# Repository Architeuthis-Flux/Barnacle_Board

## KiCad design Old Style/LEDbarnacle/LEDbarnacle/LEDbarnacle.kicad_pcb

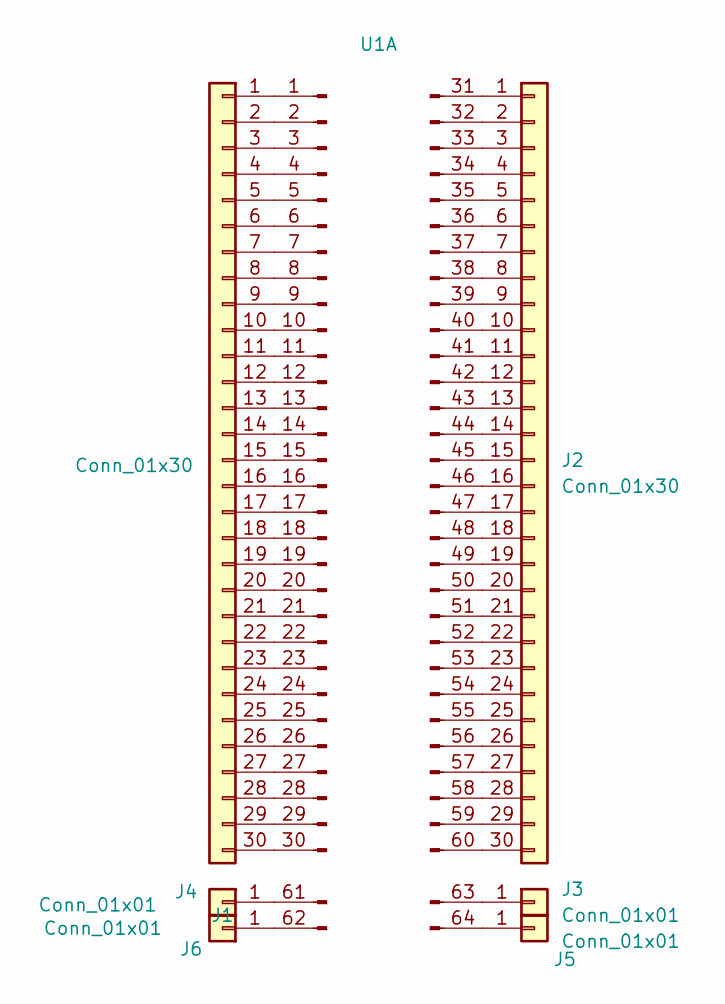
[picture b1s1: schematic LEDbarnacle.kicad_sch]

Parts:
J1, J2: Conn_01x30; ProtoboardRow
J3, J4, J5, J6: Conn_01x01; ProtoPower
U1: HEE70LP03BK_CardSide

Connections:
unnamed: J1.1, U1.1
unnamed: J1.2, U1.2
unnamed: J1.3, U1.3
unnamed: J1.4, U1.4
unnamed: J1.5, U1.5
unnamed: J1.6, U1.6
unnamed: J1.7, U1.7
unnamed: J1.8, U1.8
unnamed: J1.9, U1.9
unnamed: J1.10, U1.10
unnamed: J1.11, U1.11
unnamed: J1.12, U1.12
unnamed: J1.13, U1.13
unnamed: J1.14, U1.14
unnamed: J1.15, U1.15
unnamed: J1.16, U1.16
unnamed: J1.17, U1.17
unnamed: J1.18, U1.18
unnamed: J1.19, U1.19
unnamed: J1.20, U1.20
unnamed: J1.21, U1.21
unnamed: J1.22, U1.22
unnamed: J1.23, U1.23
unnamed: J1.24, U1.24
unnamed: J1.25, U1.25
unnamed: J1.26, U1.26
unnamed: J1.27, U1.27
unnamed: J1.28, U1.28
unnamed: J1.29, U1.29
unnamed: J1.30, U1.30
unnamed: J2.1, U1.31
unnamed: J2.2, U1.32 (Pin_0)
unnamed: J2.3, U1.33 (Pin_1)
unnamed: J2.4, U1.34 (Pin_2)
unnamed: J2.5, U1.35 (Pin_3)
unnamed: J2.6, U1.36 (Pin_4)
unnamed: J2.7, U1.37 (Pin_5)
unnamed: J2.8, U1.38 (Pin_6)
unnamed: J2.9, U1.39 (Pin_7)
unnamed: J2.10, U1.40 (Pin_8)
unnamed: J2.11, U1.41 (Pin_9)
unnamed: J2.12, U1.42 (Pin_10)
unnamed: J2.13, U1.43 (Pin_11)
unnamed: J2.14, U1.44 (Pin_12)
unnamed: J2.15, U1.45 (Pin_13)
unnamed: J2.16, U1.46 (Pin_14)
unnamed: J2.17, U1.47 (Pin_15)
unnamed: J2.18, U1.48 (Pin_16)
unnamed: J2.19, U1.49 (Pin_17)
unnamed: J2.20, U1.50 (Pin_18)
unnamed: J2.21, U1.51 (Pin_19)
unnamed: J2.22, U1.52 (Pin_20)
unnamed: J2.23, U1.53 (Pin_21)
unnamed: J2.24, U1.54 (Pin_22)
unnamed: J2.25, U1.55 (Pin_23)
unnamed: J2.26, U1.56 (Pin_24)
unnamed: J2.27, U1.57 (Pin_25)
unnamed: J2.28, U1.58 (Pin_26)
unnamed: J2.29, U1.59 (Pin_27)
unnamed: J2.30, U1.60 (Pin_28)
unnamed: J3.1, U1.63 (Bot_Pos)
unnamed: J4.1, U1.61 (Top_Pos)
unnamed: J5.1, U1.64 (Bot_Neg)
unnamed: J6.1, U1.62 (Top_Neg)

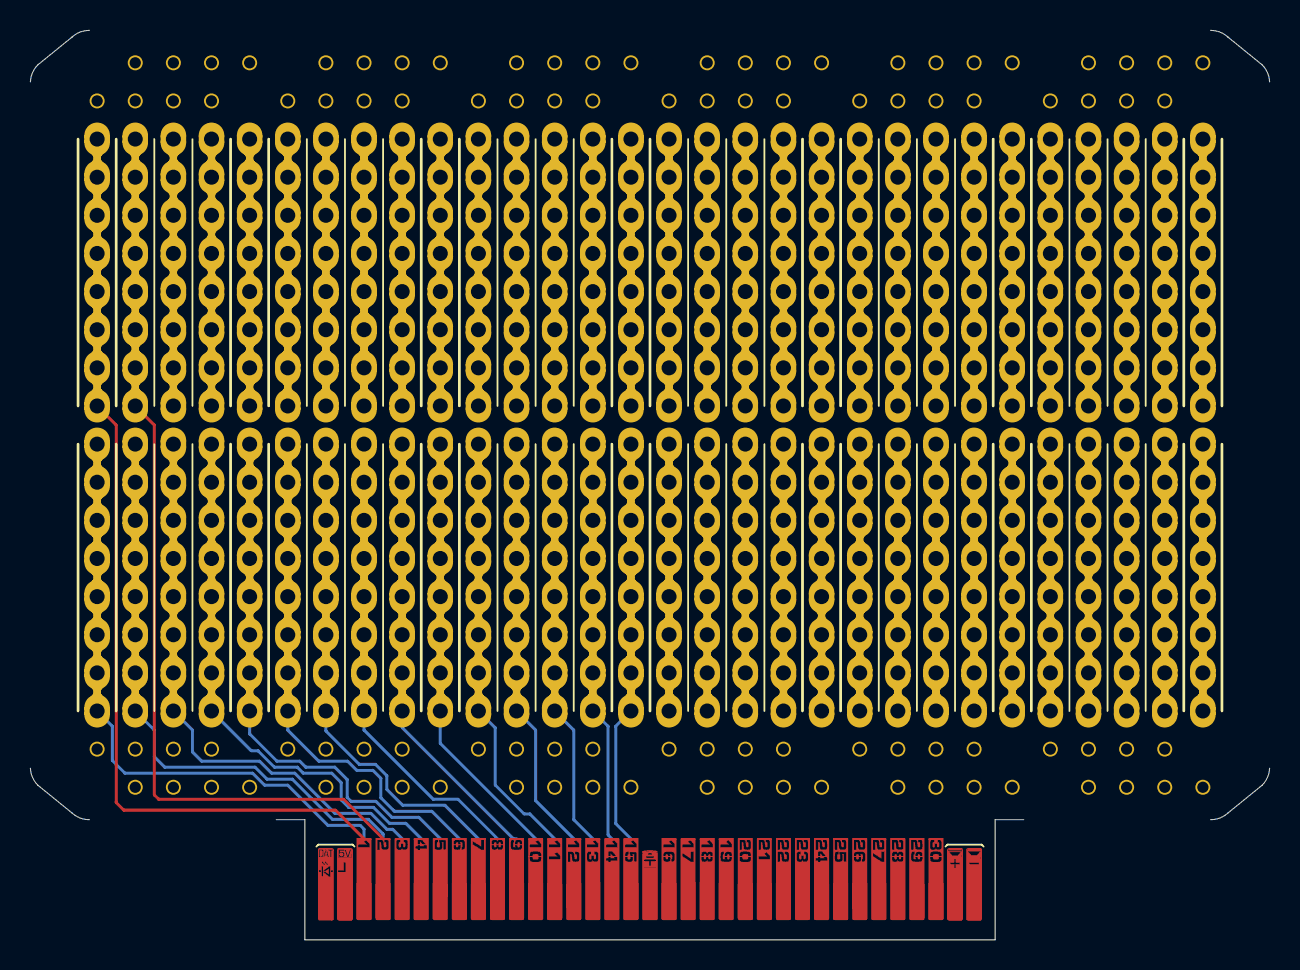
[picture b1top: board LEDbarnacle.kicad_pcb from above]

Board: 4 copper layers, 82.6 x 60.6 mm, 7 parts (0 on the bottom side), 64 nets.

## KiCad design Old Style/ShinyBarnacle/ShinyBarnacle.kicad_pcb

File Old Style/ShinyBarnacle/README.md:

# Shiny Barnacle

The Shiny Barnacle doesn't interact with the breadboard directly, but provides driver for the LEDs and a way to load/store different circuits from text files loaded into the RP2040's flash over USB, with some buttons and a knob for selecting and making nets. They can also include sequence information so a teacher can load a lab onto the students' boards and each step for building a circuit will be lit up as they build it.

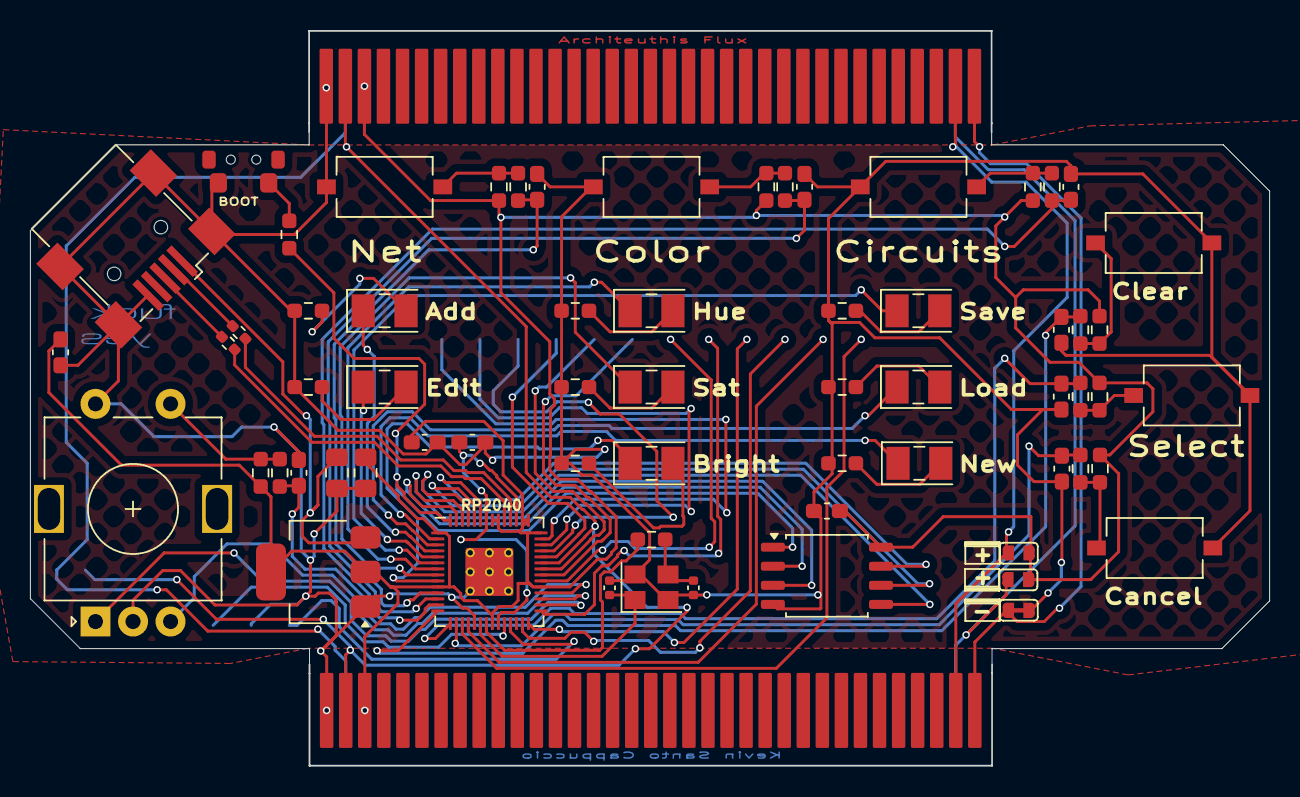
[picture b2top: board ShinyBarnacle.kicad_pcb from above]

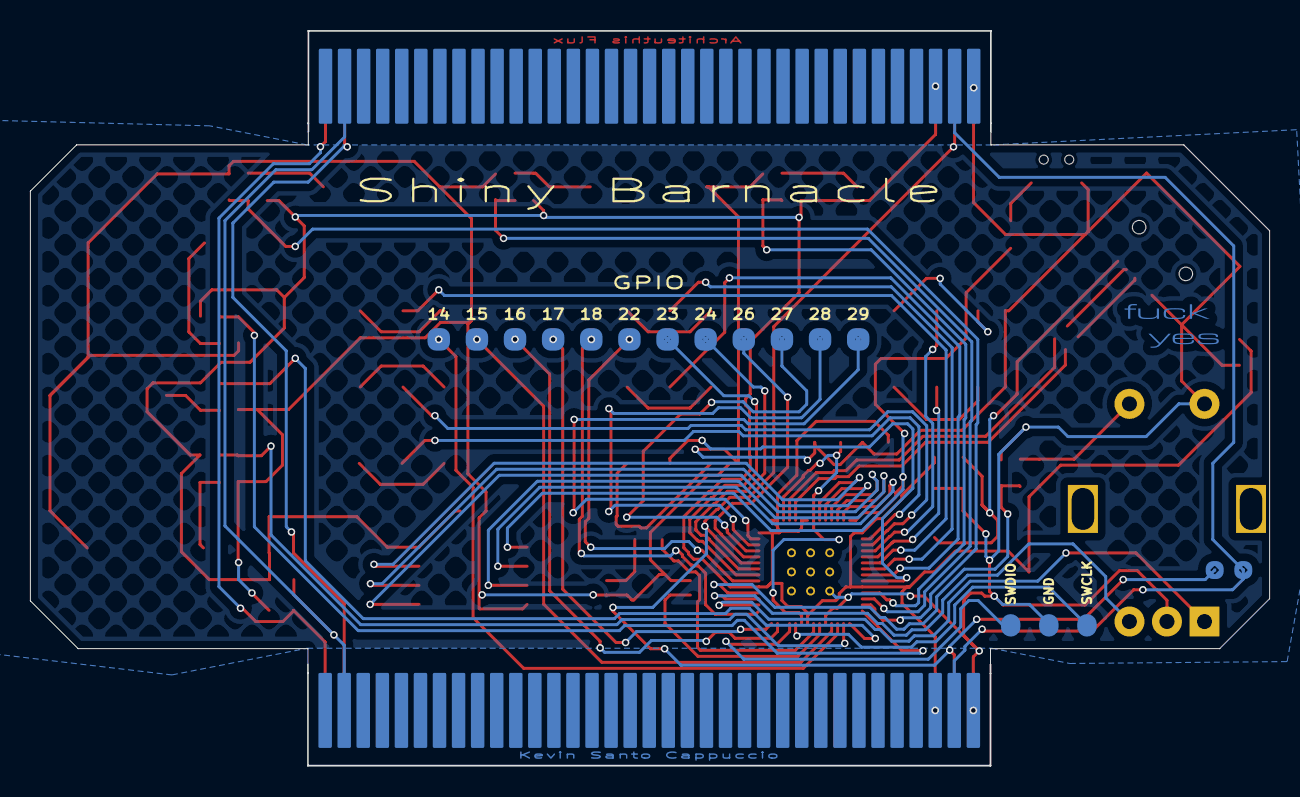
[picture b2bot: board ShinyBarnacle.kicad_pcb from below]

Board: 2 copper layers, 82.5 x 48.9 mm, 82 parts (15 on the bottom side), 130 nets.

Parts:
C1, C2: 27p; C_0402_1005Metric
C3, C5, C7, C9: 1u; C_0603_1608Metric_Pad1.08x0.95mm_HandSolder
C4, C6: 10u; C_0805_2012Metric_Pad1.18x1.45mm_HandSolder
C10, C11, C12, C13, C14, C15, C16: 0.1uF; C_0603_1608Metric_Pad1.08x0.95mm_HandSolder
D2, D3, D4, D5, D6, D7, D8, D9: LED; LED_PLCC-2_3x2mm_AK
J1: USB_B_Mini; USB_Mini-B_Wuerth_65100516121_Horizontal
J2: Debug; PinHeader_1x03_P2.54mm_Vertical
J3: Conn_02x35_JumperluxCardEdge; HEE70LP03BK_Daughter_Penis_Top
J4: Conn_02x35_JumperluxCardEdge; HEE70LP03BK_Daughter_Penis
JP1: SolderJumper_2_Bridged; SolderJumper_2_Bridged_Small
JP2, JP3: Power_From_Breadboard; SolderJumper_2_Open_Small
R1, R2: 1k; R_0603_1608Metric_Pad0.98x0.95mm_HandSolder
R3, R4: 22R; R_0402_1005Metric_Pad0.72x0.64mm_HandSolder
R5, R6, R7, R8, R9, R10, R11, R12: 1K; R_0603_1608Metric_Pad0.98x0.95mm_HandSolder
R13, R21, R22, R23, R24, R25, R26: 47K; R_0603_1608Metric_Pad0.98x0.95mm_HandSolder
R14, R15, R16, R17, R18, R19, R20: 10K; R_0603_1608Metric_Pad0.98x0.95mm_HandSolder
SW1: USB BOOT; Tact_Switch_TS24CA
SW3: Select Row; RotaryEncoder_Alps_EC11E-Switch_Vertical_H20mm
SW4, SW5, SW6, SW7, SW8, SW9: SW_Push; SW_Tactile_SPST_NO_Straight_CK_PTS636Sx25SMTRLFS
TP1, TP2, TP3, TP4, TP5, TP6, TP7, TP8, TP9, TP10, TP11, TP12: TestPoint; TestPoint_Pad_D1.0mm
TP13, TP14: TestPoint; TestPoint_D0.75mm
U1: W25Q128JVS; SOIC-8_5.23x5.23mm_P1.27mm
U2: NCP1117-3.3_SOT223; SOT-223-3_TabPin2
U3: RP2040; RP2040-QFN-56
Y1: ABLS-12.000MHZ-B4-T; Crystal_SMD_3225-4Pin_3.2x2.5mm

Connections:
1: J3.31, J4.31
2: J3.32, J4.32
3: J3.33, J4.33
4: J3.34, J4.34
5: J3.35, J4.35
6: J3.36, J4.36
7: J3.37, J4.37
8: J3.38, J4.38
9: J3.39, J4.39
10: J3.40, J4.40
11: J3.41, J4.41
12: J3.42, J4.42
13: J3.43, J4.43
14: J3.44, J4.44
15: J3.45, J4.45
16: J3.46, J4.46
17: J3.47, J4.47
18: J3.48, J4.48
19: J3.49, J4.49
20: J3.50, J4.50
21: J3.51, J4.51
22: J3.52, J4.52
23: J3.53, J4.53
24: J3.54, J4.54
25: J3.55, J4.55
26: J3.56, J4.56
27: J3.57, J4.57
28: J3.58, J4.58
29: J3.59, J4.59
30: J3.60, J4.60
31: J3.1, J4.1
32: J3.2, J4.2
33: J3.3, J4.3
34: J3.4, J4.4
35: J3.5, J4.5
36: J3.6, J4.6
37: J3.7, J4.7
38: J3.8, J4.8
39: J3.9, J4.9
40: J3.10, J4.10
41: J3.11, J4.11
42: J3.12, J4.12
43: J3.13, J4.13
44: J3.14, J4.14
45: J3.15, J4.15
46: J3.16, J4.16
47: J3.17, J4.17
48: J3.18, J4.18
49: J3.19, J4.19
50: J3.20, J4.20
51: J3.21, J4.21
52: J3.22, J4.22
53: J3.23, J4.23
54: J3.24, J4.24
55: J3.25, J4.25
56: J3.26, J4.26
57: J3.27, J4.27
58: J3.28, J4.28
59: J3.29, J4.29
60: J3.30, J4.30
+1V1: C7.1, U3.23 (DVDD), U3.45 (VREG_VOUT), U3.50 (DVDD)
+5V: C4.1, J1.1 (VBUS), U2.3 (VI)
/QSPI_SCLK: U1.6 (CLK), U3.52 (QSPI_SCLK)
/QSPI_SD0: U1.5 (DI(IO0)), U3.53 (QSPI_SD0)
/QSPI_SD1: U1.2 (DO(IO1)), U3.55 (QSPI_SD1)
/QSPI_SD2: U1.3 (IO2), U3.54 (QSPI_SD2)
/QSPI_SD3: U1.7 (IO3), U3.51 (QSPI_SD3)
/QSPI_SS: R1.1, U1.1 (~CS), U3.56 (QSPI_SS)
/SWCLK: J2.1, U3.24 (SWCLK)
/SWD: J2.3, U3.25 (SWD)
/USB_D+: J1.3 (D+), R3.1
/USB_D-: J1.2 (D-), R4.1
/XIN: C1.1, U3.20 (XIN), Y1.1
/XOUT: R2.1, U3.21 (XOUT)
/~USB_BOOT: R1.2, SW1.2
BOTTOM_RAIL_NEG: J3.62, J4.62
BOTTOM_RAIL_POS: J3.61, J4.61, JP3.1 (A)
Button_Cancel: C14.1, R18.1, U3.16 (GPIO13)
Button_Circuits: C12.1, R16.1, U3.13 (GPIO10)
Button_Clear: C11.1, R15.1, U3.14 (GPIO11)
Button_Color: C15.1, R19.1, U3.12 (GPIO9)
Button_Net: C16.1, R20.1, U3.11 (GPIO8)
Button_Select: C13.1, R17.1, U3.15 (GPIO12)
ENC_1_A: SW3.A, U3.30 (GPIO19)
ENC_1_B: SW3.B, U3.31 (GPIO20)
ENC_1_Button: C10.1, R14.1, U3.32 (GPIO21)
GPIO_14: TP1.1, U3.17 (GPIO14)
GPIO_15: TP2.1, U3.18 (GPIO15)
GPIO_18: TP5.1, U3.29 (GPIO18)
GPIO_22: TP8.1, U3.34 (GPIO22)
GPIO_23: TP9.1, U3.35 (GPIO23)
GPIO_24: TP10.1, U3.36 (GPIO24)
GPIO_26: TP11.1, U3.38 (GPIO26_ADC0)
GPIO_27: TP12.1, U3.39 (GPIO27_ADC1)
GPIO_28: TP6.1, U3.40 (GPIO28_ADC2)
GPIO_29: TP7.1, U3.41 (GPIO29_ADC3)
LED_0: D2.2 (A), U3.2 (GPIO0)
LED_1: D3.2 (A), U3.3 (GPIO1)
LED_2: D4.2 (A), U3.4 (GPIO2)
LED_3: D5.2 (A), U3.5 (GPIO3)
LED_4: D6.2 (A), U3.6 (GPIO4)
LED_5: D7.2 (A), U3.7 (GPIO5)
LED_5V: C3.1, C5.1, C6.1, C9.1, J3.67, J3.70, J4.67, J4.70, JP2.2 (B), JP3.2 (B), R13.2, R21.2, R22.2, R23.2, R24.2, R25.2, R26.2, U1.8 (VCC), U2.2 (VO), U3.1 (IOVDD), U3.10 (IOVDD), U3.22 (IOVDD), U3.33 (IOVDD), U3.42 (IOVDD), U3.43 (ADC_AVDD), U3.44 (VREG_IN), U3.48 (USB_VDD), U3.49 (IOVDD)
LED_6: D8.2 (A), U3.8 (GPIO6)
LED_7: D9.2 (A), U3.9 (GPIO7)
LED_DATA_IN: J3.69, J4.69, TP13.1
LED_DATA_OUT: J3.66, J4.66, TP14.1, U3.37 (GPIO25)
LED_GND: C1.2, C2.2, C3.2, C4.2, C5.2, C6.2, C7.2, C9.2, C10.2, C11.2, C12.2, C13.2, C14.2, C15.2, C16.2, J1.5 (GND), J1.6 (Shield), J2.2, J3.65, J3.68, J4.65, J4.68, JP1.1 (A), R5.2, R6.2, R7.2, R8.2, R9.2, R10.2, R11.2, R12.2, SW1.1, SW3.C, SW3.S2, SW4.1, SW5.1, SW6.1, SW7.1, SW8.1, SW9.1, U1.4 (GND), U2.1 (GND), U3.19 (TESTEN), U3.57 (GND), Y1.2, Y1.4
unnamed: C2.1, R2.2, Y1.3
unnamed: D2.1 (K), R5.1
unnamed: D3.1 (K), R6.1
unnamed: D4.1 (K), R7.1
unnamed: D5.1 (K), R8.1
unnamed: D6.1 (K), R9.1
unnamed: D7.1 (K), R10.1
unnamed: D8.1 (K), R11.1
unnamed: D9.1 (K), R12.1
unnamed: R13.1, R14.2, SW3.S1
unnamed: R15.2, R21.1, SW4.2
unnamed: R16.2, R22.1, SW5.2
unnamed: R17.2, R23.1, SW6.2
unnamed: R18.2, R24.1, SW7.2
unnamed: R19.2, R25.1, SW8.2
unnamed: R20.2, R26.1, SW9.2
unnamed: R4.2, U3.46 (USB_DM)
unnamed: R3.2, U3.47 (USB_DP)
TOP_RAIL_NEG: J3.64, J4.64, JP1.2 (B)
TOP_RAIL_POS: J3.63, J4.63, JP2.1 (A)
UART_Rx: TP4.1, U3.28 (GPIO17)
UART_Tx: TP3.1, U3.27 (GPIO16)

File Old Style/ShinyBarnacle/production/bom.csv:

Designator,Footprint,Quantity,Value,LCSC Part #
"C1, C2",0402,2,27p,
"C10, C11, C12, C13, C14, C15, C16",0603,7,0.1uF,
"C3, C5, C7, C9",0603,4,1u,
"C4, C6",0805,2,10u,
"D2, D3, D4, D5, D6, D7, D8, D9",LED_PLCC-2_3x2mm_AK,8,LED,
J1,USB_Mini-B_Wuerth_65100516121_Horizontal,1,USB_B_Mini,
J2,PinHeader_1x03_P2.54mm_Vertical,1,Debug,
J3,HEE70LP03BK_Daughter_Penis_Top,1,Conn_02x35_JumperluxCardEdge,
J4,HEE70LP03BK_Daughter_Penis,1,Conn_02x35_JumperluxCardEdge,
JP1,SolderJumper_2_Bridged_Small,1,SolderJumper_2_Bridged,
"JP2, JP3",SolderJumper_2_Open_Small,2,Power_From_Breadboard,
"R1, R10, R11, R12, R2, R5, R6, R7, R8, R9",0603,10,1k,
"R13, R21, R22, R23, R24, R25, R26",0603,7,47K,
"R14, R15, R16, R17, R18, R19, R20",0603,7,10K,
"R3, R4",0402,2,22R,
SW1,Tact_Switch_TS24CA,1,USB BOOT,
SW3,RotaryEncoder_Alps_EC11E-Switch_Vertical_H20mm,1,Select Row,
"SW4, SW5, SW6, SW7, SW8, SW9",SW_Tactile_SPST_NO_Straight_CK_PTS636Sx25SMTRLFS,6,SW_Push,
"TP1, TP10, TP11, TP12, TP2, TP3, TP4, TP5, TP6, TP7, TP8, TP9",TestPoint_Pad_D1.0mm,12,TestPoint,
"TP13, TP14",TestPoint_D0.75mm,2,TestPoint,
U1,SOIC-8_5.23x5.23mm_P1.27mm,1,W25Q128JVS,
U2,SOT-223-3_TabPin2,1,NCP1117-3.3_SOT223,
U3,RP2040-QFN-56,1,RP2040,
Y1,Crystal_SMD_3225-4Pin_3.2x2.5mm,1,ABLS-12.000MHZ-B4-T,

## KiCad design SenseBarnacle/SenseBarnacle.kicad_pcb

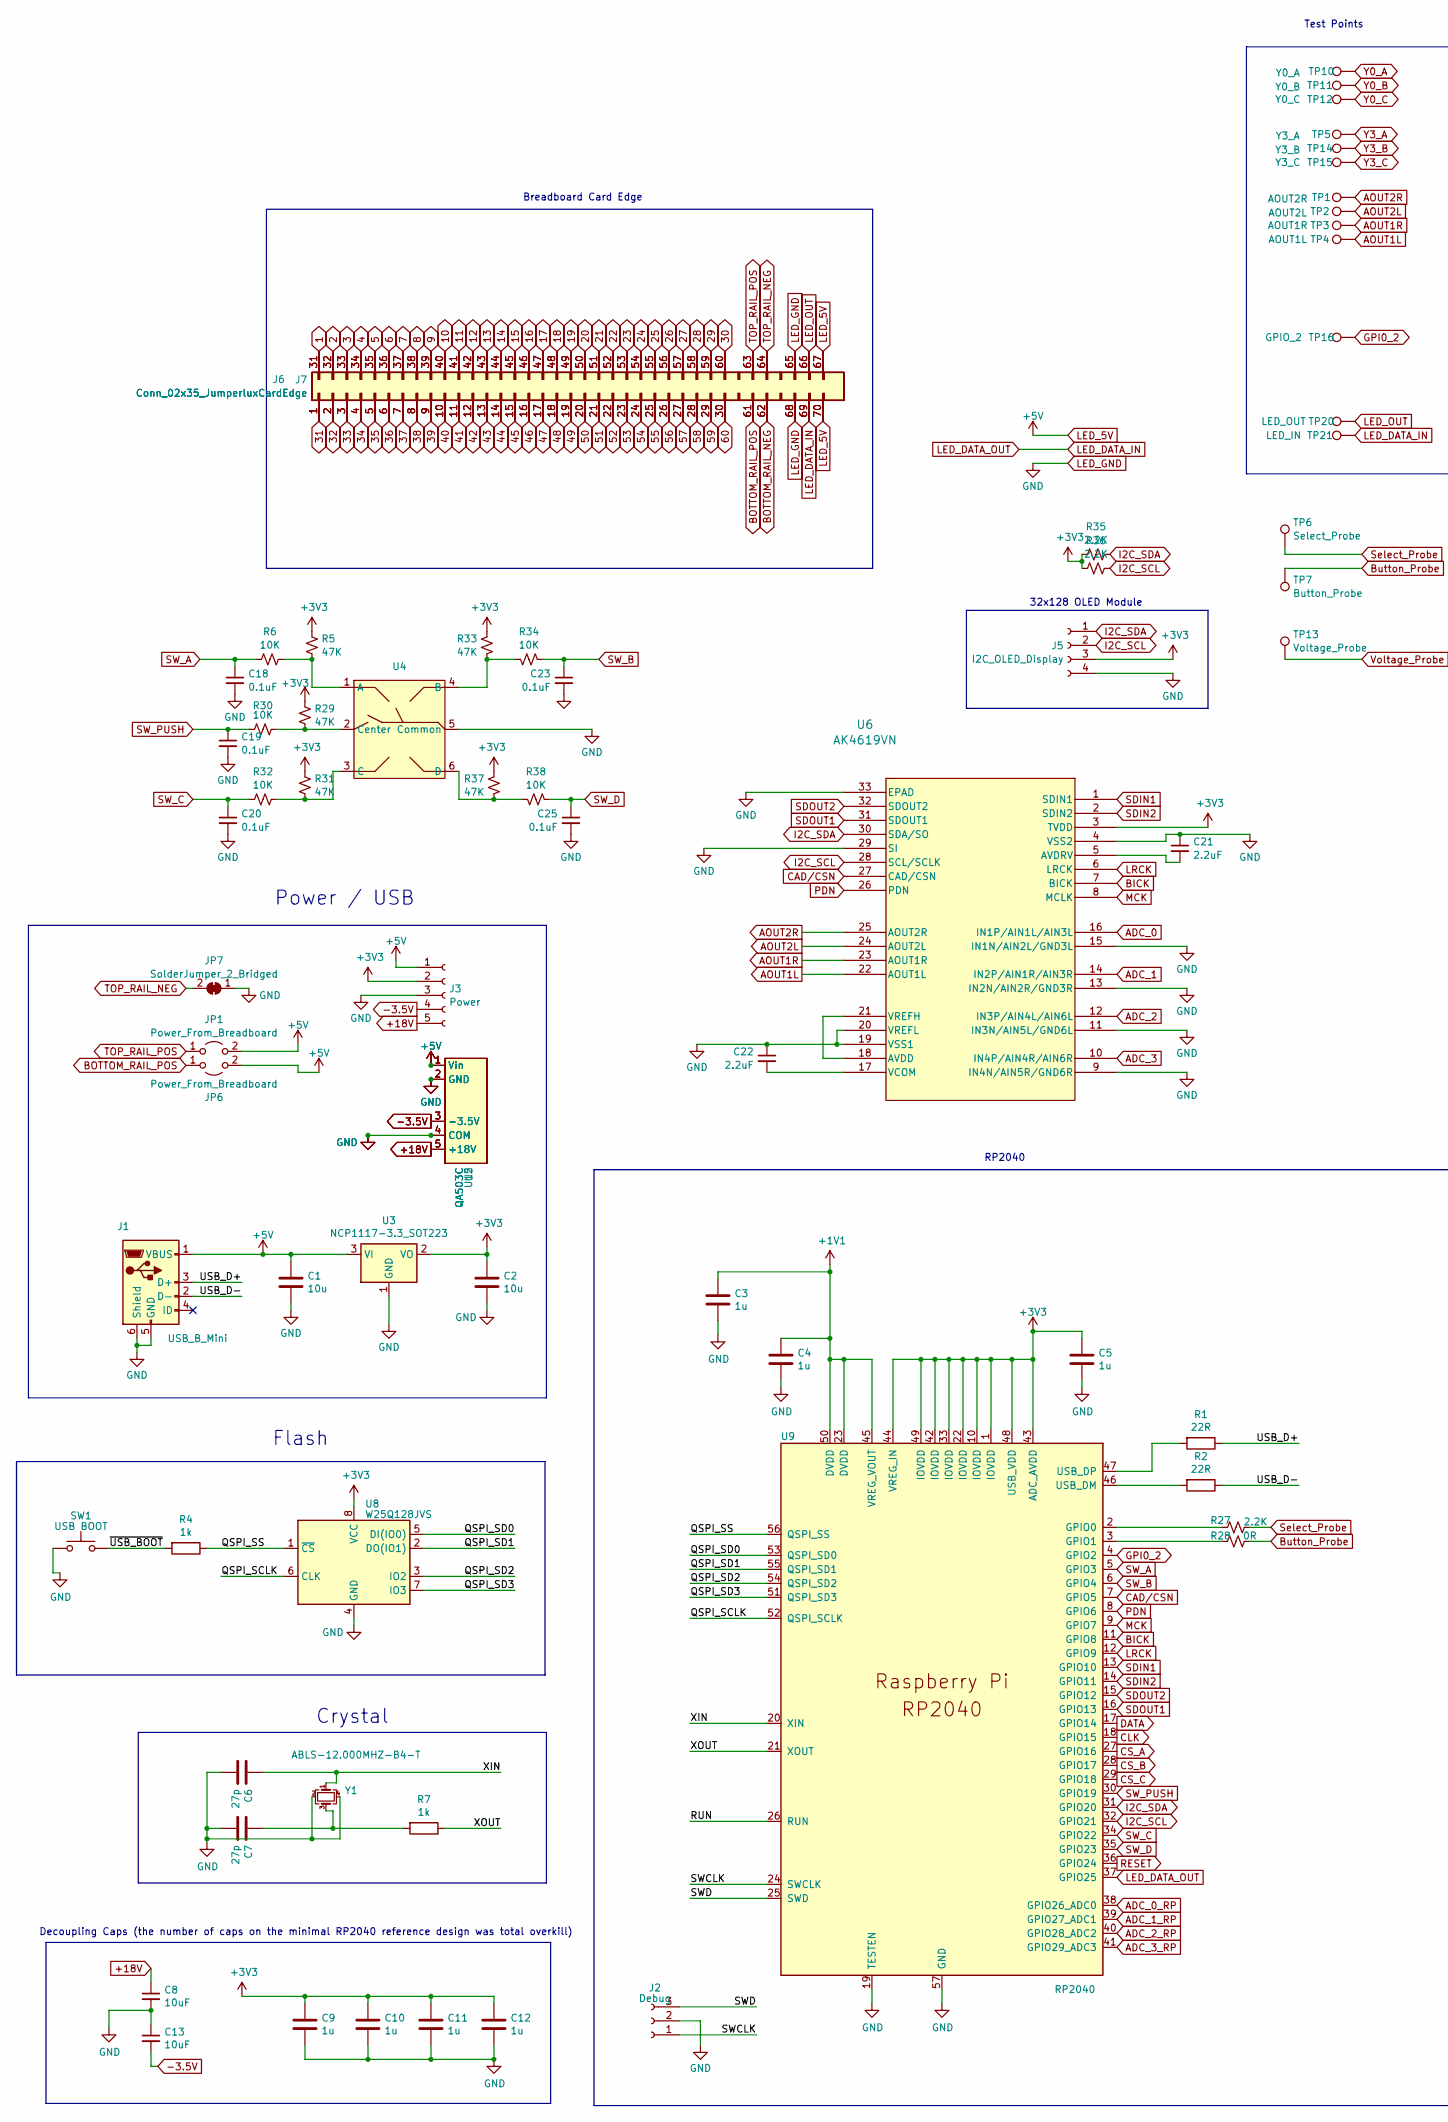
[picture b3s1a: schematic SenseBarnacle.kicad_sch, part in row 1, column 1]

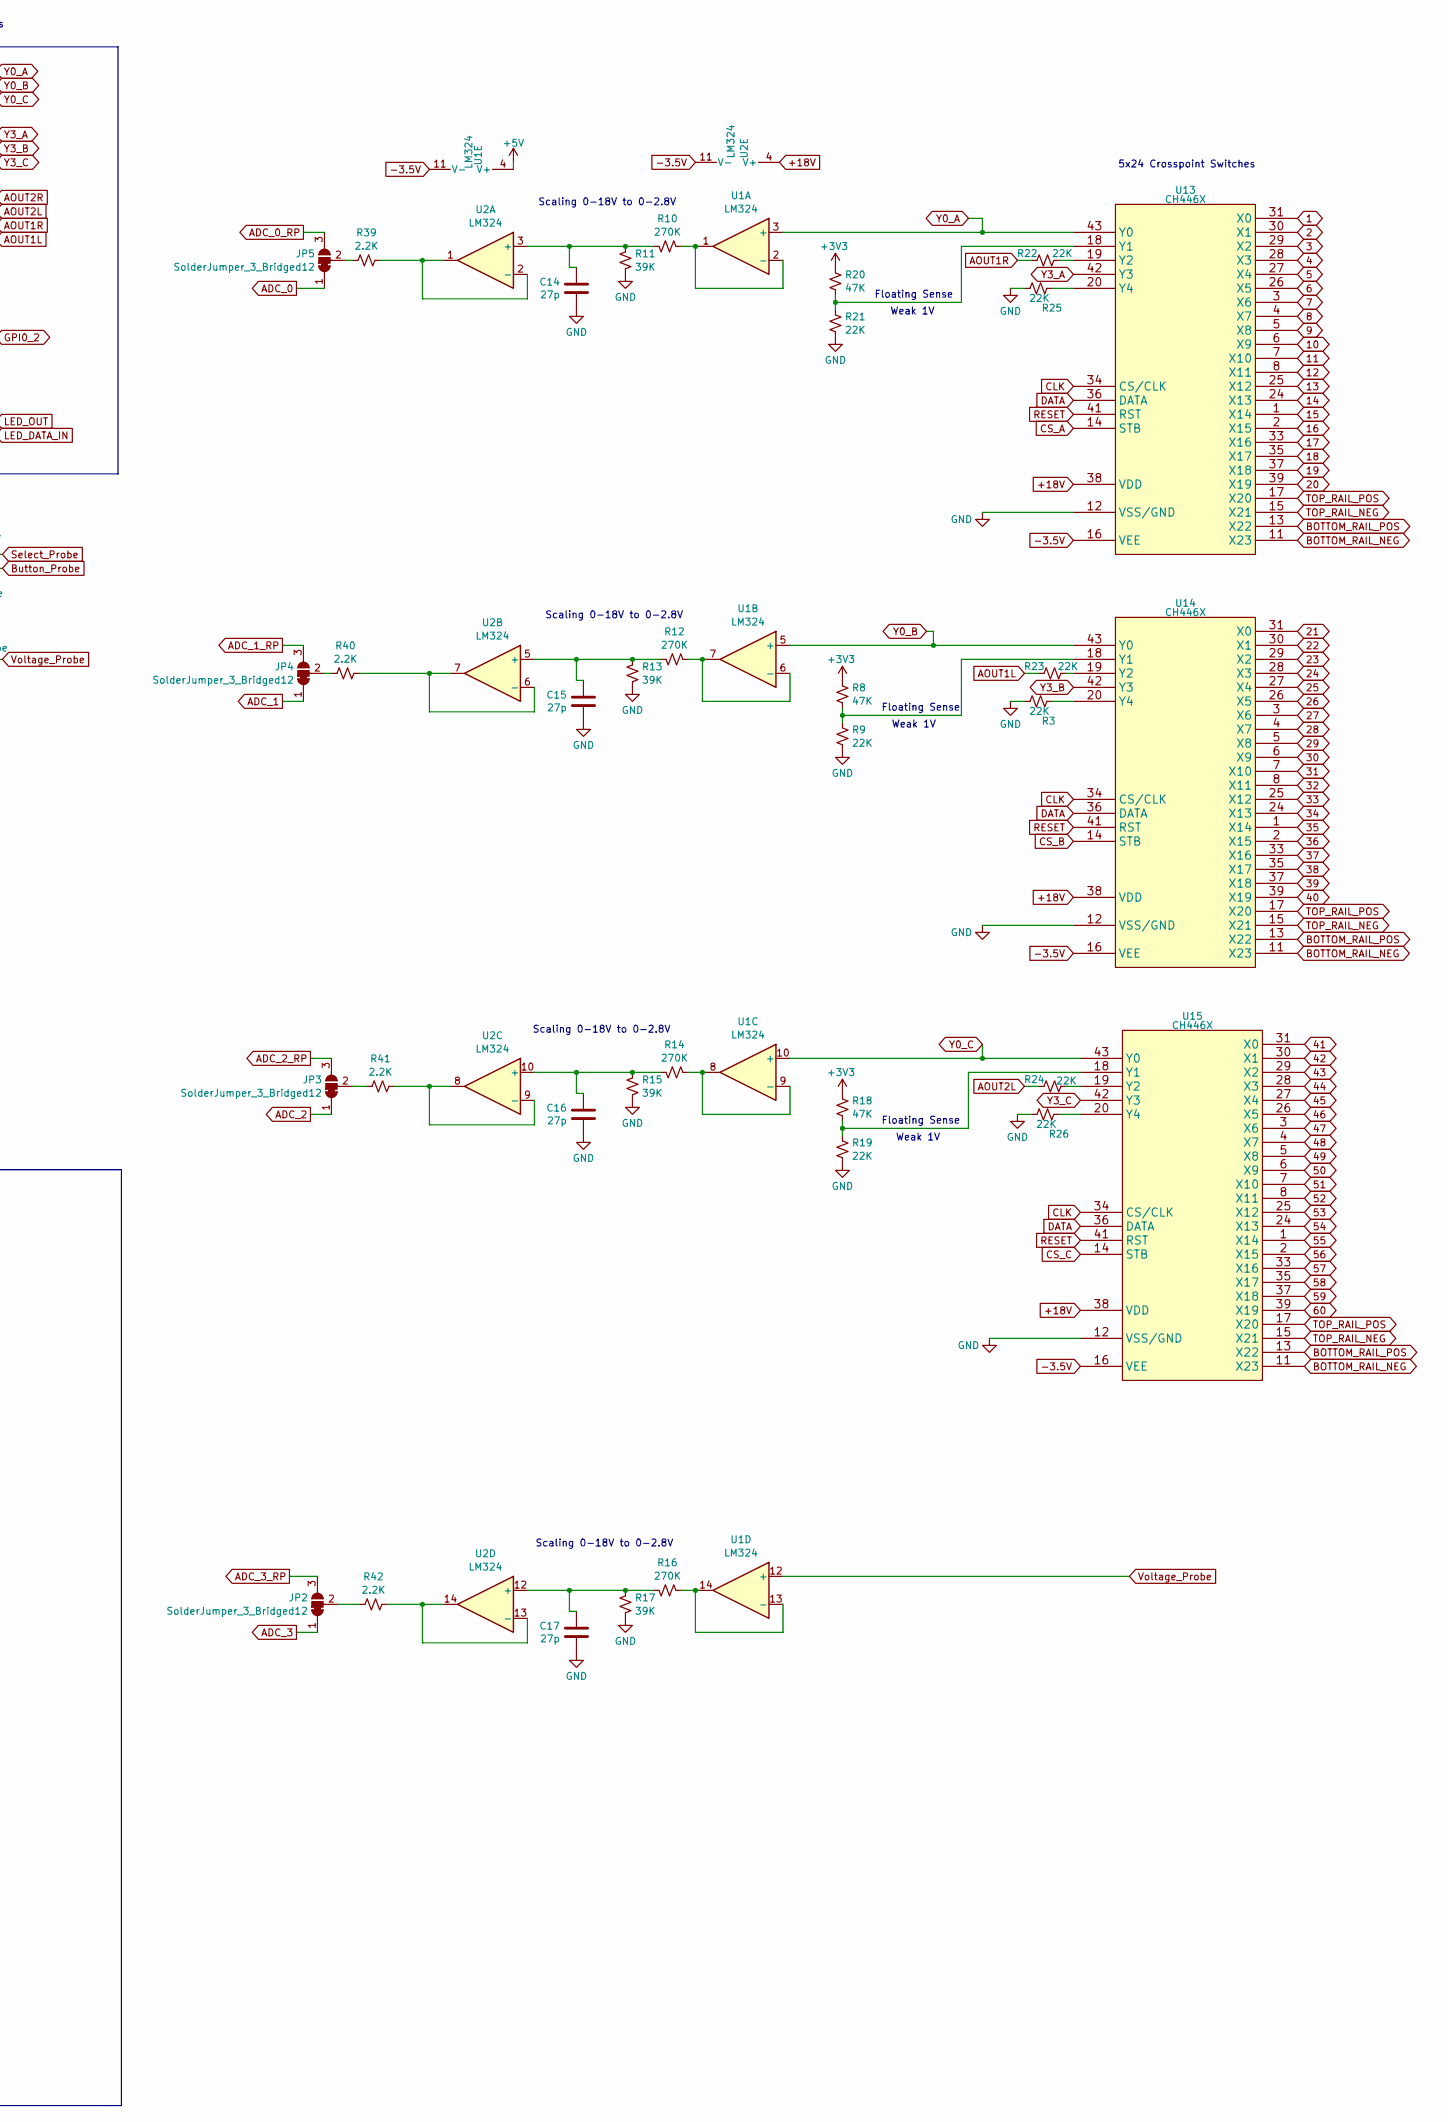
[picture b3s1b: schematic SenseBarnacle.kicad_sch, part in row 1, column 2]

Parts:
C1, C2: 10u; C_0805_2012Metric_Pad1.18x1.45mm_HandSolder
C3, C4, C5, C9, C10, C11, C12: 1u; C_0603_1608Metric_Pad1.08x0.95mm_HandSolder
C6, C7, C14, C15, C16, C17: 27p; C_0402_1005Metric
C8, C13: 10uF; C_0805_2012Metric_Pad1.18x1.45mm_HandSolder
C18, C19, C20, C23, C25: 0.1uF; C_0603_1608Metric_Pad1.08x0.95mm_HandSolder
C21, C22: 2.2uF; C_0805_2012Metric_Pad1.18x1.45mm_HandSolder
J1: USB_B_Mini; USB_Mini-B_Wuerth_65100516121_Horizontal
J2: Debug; PinHeader_1x03_P2.54mm_Vertical
J3: Power; PinHeader_1x05_P2.54mm_Vertical
J5: I2C_OLED_Display; PinHeader_1x04_P2.54mm_Vertical
J6: Conn_02x35_JumperluxCardEdge; HEE70LP03BK_Daughter_Penis_Top
J7: Conn_02x35_JumperluxCardEdge; HEE70LP03BK_Daughter_Penis
JP1, JP6: Power_From_Breadboard; SolderJumper_2_Open_Small
JP2, JP3, JP4, JP5: SolderJumper_3_Bridged12; SolderJumper-3_P1.3mm_Bridged2Bar12_RoundedPad1.0x1.5mm
JP7: SolderJumper_2_Bridged; SolderJumper_2_Bridged_Small
R1, R2: 22R; R_0402_1005Metric_Pad0.72x0.64mm_HandSolder
R3, R9, R19, R21, R22, R23, R24, R25, R26: 22K; R_0805_2012Metric_Pad1.20x1.40mm_HandSolder
R4, R7: 1k; R_0603_1608Metric_Pad0.98x0.95mm_HandSolder
R5, R8, R18, R20, R29, R31, R33, R37: 47K; R_0805_2012Metric_Pad1.20x1.40mm_HandSolder
R6, R30, R32, R34, R38: 10K; R_0805_2012Metric_Pad1.20x1.40mm_HandSolder
R10, R12, R14, R16: 270K; R_0805_2012Metric_Pad1.20x1.40mm_HandSolder
R11, R13, R15, R17: 39K; R_0805_2012Metric_Pad1.20x1.40mm_HandSolder
R27, R35, R36, R39, R40, R41, R42: 2.2K; R_0805_2012Metric_Pad1.20x1.40mm_HandSolder
R28: 0R; R_0805_2012Metric_Pad1.20x1.40mm_HandSolder
SW1: USB BOOT; SW_SPST_TL3342
TP1: AOUT2R; TestPoint_D0.75mm
TP2: AOUT2L; TestPoint_D0.75mm
TP3: AOUT1R; TestPoint_D0.75mm
TP4: AOUT1L; TestPoint_D0.75mm
TP5: Y3_A; TestPoint_D0.75mm
TP6: Select_Probe; PINHEADER-1x1_vertical
TP7: Button_Probe; PINHEADER-1x1_vertical
TP10: Y0_A; TestPoint_D0.75mm
TP11: Y0_B; TestPoint_D0.75mm
TP12: Y0_C; TestPoint_D0.75mm
TP13: Voltage_Probe; PINHEADER-1x1_vertical
TP14: Y3_B; TestPoint_D0.75mm
TP15: Y3_C; TestPoint_D0.75mm
TP16: GPIO_2; TestPoint_D0.75mm
TP20: LED_OUT; TestPoint_D0.75mm
TP21: LED_IN; TestPoint_D0.75mm
U1, U2: LM324; SOIC-14_3.9x8.7mm_P1.27mm
U3: NCP1117-3.3_SOT223; SOT-223-3_TabPin2
U4: Directional_Switch_SKRHADE010
U5, U12: QA503C
U6: AK4619VN; AK4619VN_AKM
U8: W25Q128JVS; SOIC-8_5.23x5.23mm_P1.27mm
U9: RP2040; RP2040-QFN-56
U13, U14, U15: CH446X; LQFP44_Tight
Y1: ABLS-12.000MHZ-B4-T; Crystal_SMD_3225-4Pin_3.2x2.5mm

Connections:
1: J6.31, J7.31, U13.31 (X0)
2: J6.32, J7.32, U13.30 (X1)
3: J6.33, J7.33, U13.29 (X2)
4: J6.34, J7.34, U13.28 (X3)
5: J6.35, J7.35, U13.27 (X4)
6: J6.36, J7.36, U13.26 (X5)
7: J6.37, J7.37, U13.3 (X6)
8: J6.38, J7.38, U13.4 (X7)
9: J6.39, J7.39, U13.5 (X8)
10: J6.40, J7.40, U13.6 (X9)
11: J6.41, J7.41, U13.7 (X10)
12: J6.42, J7.42, U13.8 (X11)
13: J6.43, J7.43, U13.25 (X12)
14: J6.44, J7.44, U13.24 (X13)
15: J6.45, J7.45, U13.1 (X14)
16: J6.46, J7.46, U13.2 (X15)
17: J6.47, J7.47, U13.33 (X16)
18: J6.48, J7.48, U13.35 (X17)
19: J6.49, J7.49, U13.37 (X18)
20: J6.50, J7.50, U13.39 (X19)
21: J6.51, J7.51, U14.31 (X0)
22: J6.52, J7.52, U14.30 (X1)
23: J6.53, J7.53, U14.29 (X2)
24: J6.54, J7.54, U14.28 (X3)
25: J6.55, J7.55, U14.27 (X4)
26: J6.56, J7.56, U14.26 (X5)
27: J6.57, J7.57, U14.3 (X6)
28: J6.58, J7.58, U14.4 (X7)
29: J6.59, J7.59, U14.5 (X8)
30: J6.60, J7.60, U14.6 (X9)
31: J6.1, J7.1, U14.7 (X10)
32: J6.2, J7.2, U14.8 (X11)
33: J6.3, J7.3, U14.25 (X12)
34: J6.4, J7.4, U14.24 (X13)
35: J6.5, J7.5, U14.1 (X14)
36: J6.6, J7.6, U14.2 (X15)
37: J6.7, J7.7, U14.33 (X16)
38: J6.8, J7.8, U14.35 (X17)
39: J6.9, J7.9, U14.37 (X18)
40: J6.10, J7.10, U14.39 (X19)
41: J6.11, J7.11, U15.31 (X0)
42: J6.12, J7.12, U15.30 (X1)
43: J6.13, J7.13, U15.29 (X2)
44: J6.14, J7.14, U15.28 (X3)
45: J6.15, J7.15, U15.27 (X4)
46: J6.16, J7.16, U15.26 (X5)
47: J6.17, J7.17, U15.3 (X6)
48: J6.18, J7.18, U15.4 (X7)
49: J6.19, J7.19, U15.5 (X8)
50: J6.20, J7.20, U15.6 (X9)
51: J6.21, J7.21, U15.7 (X10)
52: J6.22, J7.22, U15.8 (X11)
53: J6.23, J7.23, U15.25 (X12)
54: J6.24, J7.24, U15.24 (X13)
55: J6.25, J7.25, U15.1 (X14)
56: J6.26, J7.26, U15.2 (X15)
57: J6.27, J7.27, U15.33 (X16)
58: J6.28, J7.28, U15.35 (X17)
59: J6.29, J7.29, U15.37 (X18)
60: J6.30, J7.30, U15.39 (X19)
+1V1: C3.1, C4.1, U9.23 (DVDD), U9.45 (VREG_VOUT), U9.50 (DVDD)
+3V3: C2.1, C5.1, C9.1, C10.1, C11.1, C12.1, J3.2, J5.3, R5.2, R8.1, R18.1, R20.1, R29.2, R31.2, R33.2, R35.1, R36.1, R37.2, U3.2 (VO), U6.3 (TVDD), U8.8 (VCC), U9.1 (IOVDD), U9.10 (IOVDD), U9.22 (IOVDD), U9.33 (IOVDD), U9.42 (IOVDD), U9.43 (ADC_AVDD), U9.44 (VREG_IN), U9.48 (USB_VDD), U9.49 (IOVDD)
+18V: C8.1, J3.5, U2.4 (V+), U5.5 (+18V), U12.5 (+18V), U13.38 (VDD), U14.38 (VDD), U15.38 (VDD)
-3.5V: C13.2, J3.4, U1.11 (V-), U2.11 (V-), U5.3 (-3.5V), U12.3 (-3.5V), U13.16 (VEE), U14.16 (VEE), U15.16 (VEE)
/QSPI_SCLK: U8.6 (CLK), U9.52 (QSPI_SCLK)
/QSPI_SD0: U8.5 (DI(IO0)), U9.53 (QSPI_SD0)
/QSPI_SD1: U8.2 (DO(IO1)), U9.55 (QSPI_SD1)
/QSPI_SD2: U8.3 (IO2), U9.54 (QSPI_SD2)
/QSPI_SD3: U8.7 (IO3), U9.51 (QSPI_SD3)
/QSPI_SS: R4.1, U8.1 (~CS), U9.56 (QSPI_SS)
/RUN: U9.26 (RUN)
/SWCLK: J2.1, U9.24 (SWCLK)
/SWD: J2.3, U9.25 (SWD)
/USB_D+: J1.3 (D+), R1.1
/USB_D-: J1.2 (D-), R2.1
/XIN: C6.1, U9.20 (XIN), Y1.1
/XOUT: R7.1, U9.21 (XOUT)
/~USB_BOOT: R4.2, SW1.2
ADC_0: JP5.1 (A), U6.16 (IN1P/AIN1L/AIN3L)
ADC_0_RP: JP5.3 (B), U9.38 (GPIO26_ADC0)
ADC_1: JP4.1 (A), U6.14 (IN2P/AIN1R/AIN3R)
ADC_1_RP: JP4.3 (B), U9.39 (GPIO27_ADC1)
ADC_2: JP3.1 (A), U6.12 (IN3P/AIN4L/AIN6L)
ADC_2_RP: JP3.3 (B), U9.40 (GPIO28_ADC2)
ADC_3: JP2.1 (A), U6.10 (IN4P/AIN4R/AIN6R)
ADC_3_RP: JP2.3 (B), U9.41 (GPIO29_ADC3)
AOUT1L: R23.2, TP4.1, U6.22 (AOUT1L)
AOUT1R: R22.2, TP3.1, U6.23 (AOUT1R)
AOUT2L: R24.2, TP2.1, U6.24 (AOUT2L)
AOUT2R: TP1.1, U6.25 (AOUT2R)
BICK: U6.7 (BICK), U9.11 (GPIO8)
BOTTOM_RAIL_NEG: J6.62, J7.62, U13.11 (X23), U14.11 (X23), U15.11 (X23)
BOTTOM_RAIL_POS: J6.61, J7.61, JP6.1 (A), U13.13 (X22), U14.13 (X22), U15.13 (X22)
Button_Probe: R28.2, TP7.1
CAD/CSN: U6.27 (CAD/CSN), U9.7 (GPIO5)
CLK: U9.18 (GPIO15), U13.34 (CS/CLK), U14.34 (CS/CLK), U15.34 (CS/CLK)
CS_A: U9.27 (GPIO16), U13.14 (STB)
CS_B: U9.28 (GPIO17), U14.14 (STB)
CS_C: U9.29 (GPIO18), U15.14 (STB)
DATA: U9.17 (GPIO14), U13.36 (DATA), U14.36 (DATA), U15.36 (DATA)
GPI0_2: TP16.1, U9.4 (GPIO2)
I2C_SCL: J5.2, R36.2, U6.28 (SCL/SCLK), U9.32 (GPIO21)
I2C_SDA: J5.1, R35.2, U6.30 (SDA/SO), U9.31 (GPIO20)
LED_5V: C1.1, J1.1 (VBUS), J3.1, J6.67, J6.70, J7.67, J7.70, JP1.2 (B), JP6.2 (B), U1.4 (V+), U3.3 (VI), U5.1 (Vin), U12.1 (Vin)
LED_DATA_IN: J6.69, J7.69, TP21.1, U9.37 (GPIO25)
LED_GND: C1.2, C2.2, C3.2, C4.2, C5.2, C6.2, C7.2, C8.2, C9.2, C10.2, C11.2, C12.2, C13.1, C14.2, C15.2, C16.2, C17.2, C18.2, C19.2, C20.2, C21.1, C22.1, C23.2, C25.2, J1.5 (GND), J1.6 (Shield), J2.2, J3.3, J5.4, J6.65, J6.68, J7.65, J7.68, JP7.1 (A), R3.2, R9.2, R11.2, R13.2, R15.2, R17.2, R19.2, R21.2, R25.2, R26.2, SW1.1, U3.1 (GND), U4.5 (Common), U5.2 (GND), U5.4 (COM), U6.4 (VSS2), U6.9 (IN4N/AIN5R/GND6R), U6.11 (IN3N/AIN5L/GND6L), U6.13 (IN2N/AIN2R/GND3R), U6.15 (IN1N/AIN2L/GND3L), U6.19 (VSS1), U6.20 (VREFL), U6.29 (SI), U6.33 (EPAD), U8.4 (GND), U9.19 (TESTEN), U9.57 (GND), U12.2 (GND), U12.4 (COM), U13.12 (VSS/GND), U14.12 (VSS/GND), U15.12 (VSS/GND), Y1.2, Y1.4
LED_OUT: J6.66, J7.66, TP20.1
LRCK: U6.6 (LRCK), U9.12 (GPIO9)
MCK: U6.8 (MCLK), U9.9 (GPIO7)
unnamed: C7.1, R7.2, Y1.3
unnamed: JP2.2 (C), R42.1
unnamed: JP3.2 (C), R41.1
unnamed: JP4.2 (C), R40.1
unnamed: JP5.2 (C), R39.1
unnamed: R10.1, U1.1, U1.2 (-)
unnamed: R12.1, U1.6 (-), U1.7
unnamed: R14.1, U1.8, U1.9 (-)
unnamed: R16.1, U1.13 (-), U1.14
unnamed: C14.1, R10.2, R11.1, U2.3 (+)
unnamed: R39.2, U2.1, U2.2 (-)
unnamed: C15.1, R12.2, R13.1, U2.5 (+)
unnamed: R40.2, U2.6 (-), U2.7
unnamed: C16.1, R14.2, R15.1, U2.10 (+)
unnamed: R41.2, U2.8, U2.9 (-)
unnamed: C17.1, R16.2, R17.1, U2.12 (+)
unnamed: R42.2, U2.13 (-), U2.14
unnamed: R5.1, R6.2, U4.1 (A)
unnamed: R33.1, R34.2, U4.4 (B)
unnamed: R31.1, R32.2, U4.3 (C)
unnamed: R29.1, R30.2, U4.2 (Center)
unnamed: R37.1, R38.2, U4.6 (D)
unnamed: U6.18 (AVDD), U6.21 (VREFH)
unnamed: C21.2, U6.5 (AVDRV)
unnamed: C22.2, U6.17 (VCOM)
unnamed: R27.1, U9.2 (GPIO0)
unnamed: R28.1, U9.3 (GPIO1)
unnamed: R2.2, U9.46 (USB_DM)
unnamed: R1.2, U9.47 (USB_DP)
unnamed: R20.2, R21.1, U13.18 (Y1)
unnamed: R22.1, U13.19 (Y2)
unnamed: R25.1, U13.20 (Y4)
unnamed: R8.2, R9.1, U14.18 (Y1)
unnamed: R23.1, U14.19 (Y2)
unnamed: R3.1, U14.20 (Y4)
unnamed: R18.2, R19.1, U15.18 (Y1)
unnamed: R24.1, U15.19 (Y2)
unnamed: R26.1, U15.20 (Y4)
PDN: U6.26 (PDN), U9.8 (GPIO6)
RESET: U9.36 (GPIO24), U13.41 (RST), U14.41 (RST), U15.41 (RST)
SDIN1: U6.1 (SDIN1), U9.13 (GPIO10)
SDIN2: U6.2 (SDIN2), U9.14 (GPIO11)
SDOUT1: U6.31 (SDOUT1), U9.16 (GPIO13)
SDOUT2: U6.32 (SDOUT2), U9.15 (GPIO12)
SW_A: C18.1, R6.1, U9.5 (GPIO3)
SW_B: C23.1, R34.1, U9.6 (GPIO4)
SW_C: C20.1, R32.1, U9.34 (GPIO22)
SW_D: C25.1, R38.1, U9.35 (GPIO23)
SW_PUSH: C19.1, R30.1, U9.30 (GPIO19)
Select_Probe: R27.2, TP6.1
TOP_RAIL_NEG: J6.64, J7.64, JP7.2 (B), U13.15 (X21), U14.15 (X21), U15.15 (X21)
TOP_RAIL_POS: J6.63, J7.63, JP1.1 (A), U13.17 (X20), U14.17 (X20), U15.17 (X20)
Voltage_Probe: TP13.1, U1.12 (+)
Y0_A: TP10.1, U1.3 (+), U13.43 (Y0)
Y0_B: TP11.1, U1.5 (+), U14.43 (Y0)
Y0_C: TP12.1, U1.10 (+), U15.43 (Y0)
Y3_A: TP5.1, U13.42 (Y3)
Y3_B: TP14.1, U14.42 (Y3)
Y3_C: TP15.1, U15.42 (Y3)

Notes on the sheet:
Test Points
Power / USB
32x128 OLED Module
Weak 1V
Floating Sense
Scaling 0-18V to 0-2.8V
RP2040
Breadboard Card Edge
5x24 Crosspoint Switches
Crystal
Flash
Decoupling Caps (the number of caps on the minimal RP2040 reference design was total overkill)
